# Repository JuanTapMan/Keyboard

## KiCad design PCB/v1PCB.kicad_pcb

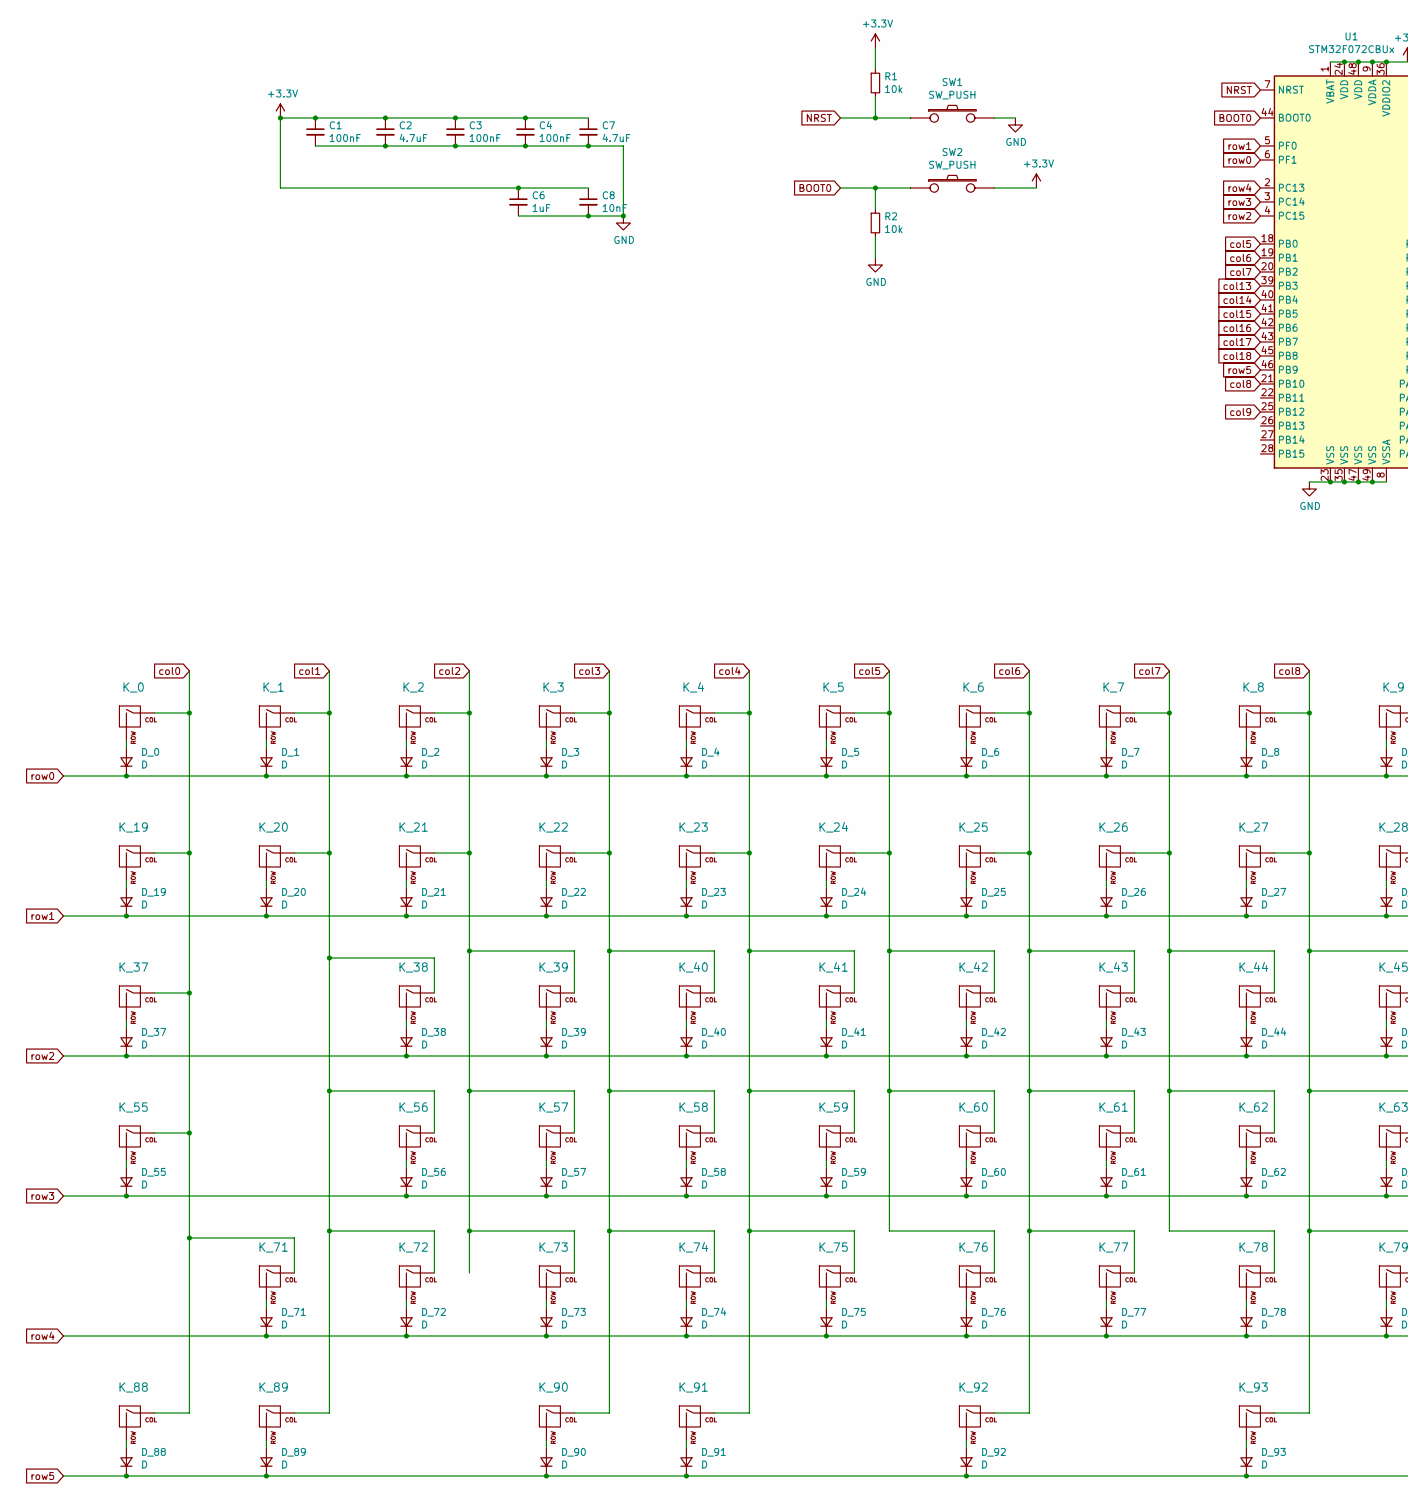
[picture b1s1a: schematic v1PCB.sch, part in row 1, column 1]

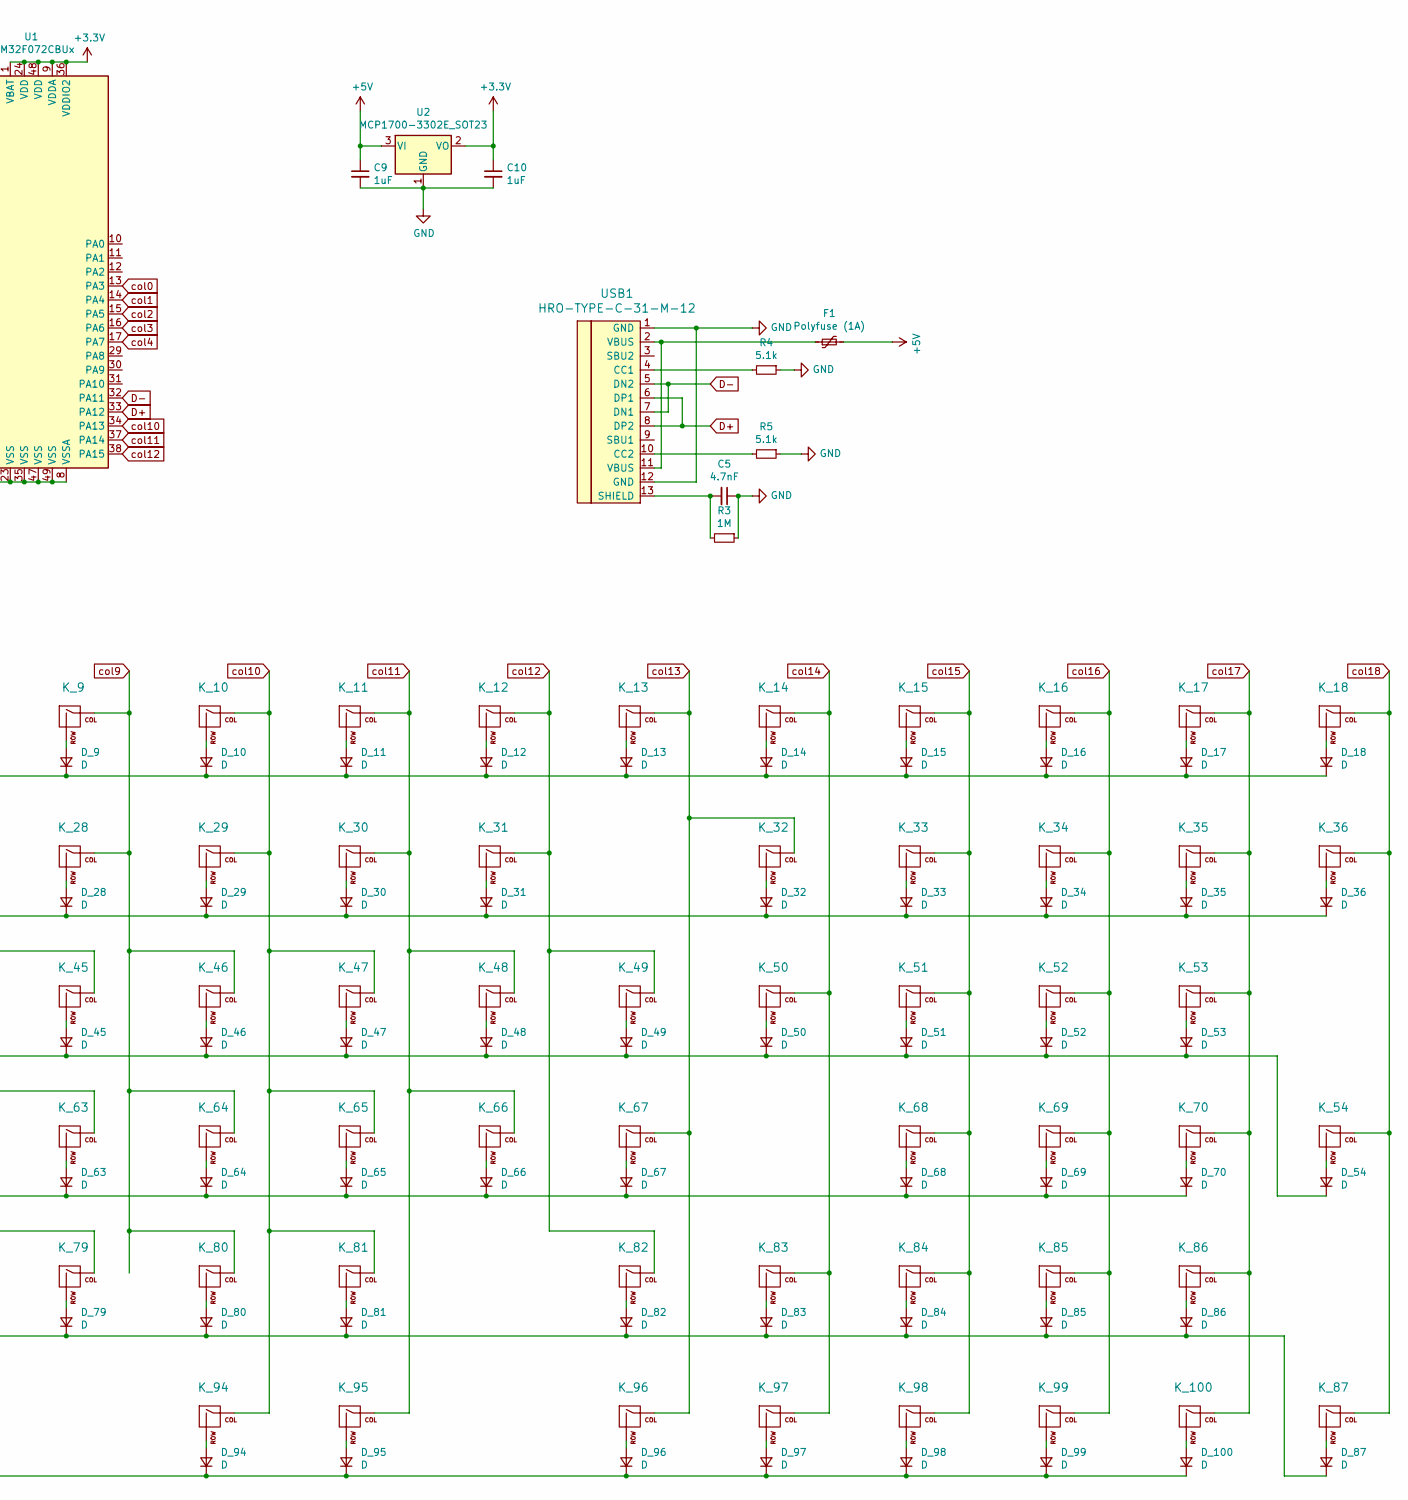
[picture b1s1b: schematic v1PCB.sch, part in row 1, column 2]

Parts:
C1, C3, C4: 100nF; C_0402_1005Metric
C2, C7: 4.7uF; C_0603_1608Metric
C5: 4.7nF; C_0603_1608Metric
C6: 1uF; C_0603_1608Metric
C8: 10nF; C_0402_1005Metric
C9, C10: 1uF; C_0402_1005Metric
D_0, D_1, D_2, D_3, D_4, D_5, D_6, D_7, D_8, D_9, D_10, D_11, D_12, D_13, D_14, D_15, D_16, D_17, D_18, D_19, D_20, D_21, D_22, D_23, D_24, D_25, D_26, D_27, D_28, D_29, D_30, D_31, D_32, D_33, D_34, D_35, D_36, D_37, D_38, D_39, D_40, D_41, D_42, D_43, D_44, D_45, D_46, D_47, D_48, D_49, D_50, D_51, D_52, D_53, D_54, D_55, D_56, D_57, D_58, D_59, D_60, D_61, D_62, D_63, D_64, D_65, D_66, D_67, D_68, D_69, D_70, D_71, D_72, D_73, D_74, D_75, D_76, D_77, D_78, D_79, D_80, D_81, D_82, D_83, D_84, D_85, D_86, D_87, D_88, D_89, D_90, D_91, D_92, D_93, D_94, D_95, D_96, D_97, D_98, D_99, D_100: D; D_SOD-123
F1: Polyfuse (1A); Fuse_0603_1608Metric
K_0, K_1, K_2, K_3, K_4, K_5, K_6, K_7, K_8, K_9, K_10, K_11, K_12, K_13, K_14, K_15, K_16, K_17, K_18, K_19, K_20, K_21, K_22, K_23, K_24, K_25, K_26, K_27, K_28, K_29, K_30, K_31, K_33, K_34, K_35, K_36, K_37, K_38, K_39, K_40, K_41, K_42, K_43, K_44, K_45, K_46, K_47, K_48, K_49, K_50, K_51, K_52, K_53, K_55, K_56, K_57, K_58, K_59, K_60, K_61, K_62, K_63, K_64, K_65, K_66, K_68, K_69, K_70, K_72, K_73, K_74, K_75, K_76, K_77, K_78, K_79, K_80, K_81, K_83, K_84, K_85, K_86, K_88, K_89, K_90, K_92, K_94, K_95, K_96, K_97, K_98, K_99, K_100: KEYSW; MXOnly-1U-NoLED
K_32, K_54, K_87: KEYSW; MXOnly-2U-NoLED
K_67, K_71, K_91: KEYSW; MXOnly-2.25U-NoLED
K_82: KEYSW; MXOnly-1.75U-NoLED
K_93: KEYSW; MXOnly-2.75U-NoLED
R1, R2: 10k; R_0805_2012Metric
R3: 1M; R_0805_2012Metric
R4, R5: 5.1k; R_0805_2012Metric
SW1, SW2: SW_PUSH; PushButton_6x6mm_TH
U1: STM32F072CBUx; QFN-48-1EP_7x7mm_P0.5mm_EP5.6x5.6mm
U2: MCP1700-3302E_SOT23; SOT-23
USB1: HRO-TYPE-C-31-M-12; HRO-TYPE-C-31-M-12-Assembly

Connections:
+3V3: C1.1, C2.1, C3.1, C4.1, C6.1, C7.1, C8.1, C10.1, R1.1, SW2.2, U1.1 (VBAT), U1.9 (VDDA), U1.24 (VDD), U1.36 (VDDIO2), U1.48 (VDD), U2.2 (VO)
+5V: C9.1, F1.2, U2.3 (VI)
BOOT0: R2.1, SW2.1, U1.44 (BOOT0)
D+: U1.33 (PA12), USB1.6 (DP1), USB1.8 (DP2)
D-: U1.32 (PA11), USB1.5 (DN2), USB1.7 (DN1)
GND: C1.2, C2.2, C3.2, C4.2, C5.1, C6.2, C7.2, C8.2, C9.2, C10.2, R2.2, R3.1, R4.1, R5.1, SW1.2, U1.8 (VSSA), U1.23 (VSS), U1.35 (VSS), U1.47 (VSS), U1.49 (VSS), U2.1 (GND), USB1.1 (GND), USB1.12 (GND)
NRST: R1.2, SW1.1, U1.7 (NRST)
unnamed: C5.2, R3.2, USB1.13 (SHIELD)
unnamed: D_0.2 (A), K_0.2 (ROW)
unnamed: D_1.2 (A), K_1.2 (ROW)
unnamed: D_2.2 (A), K_2.2 (ROW)
unnamed: D_3.2 (A), K_3.2 (ROW)
unnamed: D_4.2 (A), K_4.2 (ROW)
unnamed: D_5.2 (A), K_5.2 (ROW)
unnamed: D_6.2 (A), K_6.2 (ROW)
unnamed: D_7.2 (A), K_7.2 (ROW)
unnamed: D_8.2 (A), K_8.2 (ROW)
unnamed: D_9.2 (A), K_9.2 (ROW)
unnamed: D_10.2 (A), K_10.2 (ROW)
unnamed: D_11.2 (A), K_11.2 (ROW)
unnamed: D_12.2 (A), K_12.2 (ROW)
unnamed: D_13.2 (A), K_13.2 (ROW)
unnamed: D_14.2 (A), K_14.2 (ROW)
unnamed: D_15.2 (A), K_15.2 (ROW)
unnamed: D_16.2 (A), K_16.2 (ROW)
unnamed: D_17.2 (A), K_17.2 (ROW)
unnamed: D_18.2 (A), K_18.2 (ROW)
unnamed: D_19.2 (A), K_19.2 (ROW)
unnamed: D_20.2 (A), K_20.2 (ROW)
unnamed: D_21.2 (A), K_21.2 (ROW)
unnamed: D_22.2 (A), K_22.2 (ROW)
unnamed: D_23.2 (A), K_23.2 (ROW)
unnamed: D_24.2 (A), K_24.2 (ROW)
unnamed: D_25.2 (A), K_25.2 (ROW)
unnamed: D_26.2 (A), K_26.2 (ROW)
unnamed: D_27.2 (A), K_27.2 (ROW)
unnamed: D_28.2 (A), K_28.2 (ROW)
unnamed: D_29.2 (A), K_29.2 (ROW)
unnamed: D_30.2 (A), K_30.2 (ROW)
unnamed: D_31.2 (A), K_31.2 (ROW)
unnamed: D_32.2 (A), K_32.2 (ROW)
unnamed: D_33.2 (A), K_33.2 (ROW)
unnamed: D_34.2 (A), K_34.2 (ROW)
unnamed: D_35.2 (A), K_35.2 (ROW)
unnamed: D_36.2 (A), K_36.2 (ROW)
unnamed: D_37.2 (A), K_37.2 (ROW)
unnamed: D_38.2 (A), K_38.2 (ROW)
unnamed: D_39.2 (A), K_39.2 (ROW)
unnamed: D_40.2 (A), K_40.2 (ROW)
unnamed: D_41.2 (A), K_41.2 (ROW)
unnamed: D_42.2 (A), K_42.2 (ROW)
unnamed: D_43.2 (A), K_43.2 (ROW)
unnamed: D_44.2 (A), K_44.2 (ROW)
unnamed: D_45.2 (A), K_45.2 (ROW)
unnamed: D_46.2 (A), K_46.2 (ROW)
unnamed: D_47.2 (A), K_47.2 (ROW)
unnamed: D_48.2 (A), K_48.2 (ROW)
unnamed: D_49.2 (A), K_49.2 (ROW)
unnamed: D_50.2 (A), K_50.2 (ROW)
unnamed: D_51.2 (A), K_51.2 (ROW)
unnamed: D_52.2 (A), K_52.2 (ROW)
unnamed: D_53.2 (A), K_53.2 (ROW)
unnamed: D_54.2 (A), K_54.2 (ROW)
unnamed: D_55.2 (A), K_55.2 (ROW)
unnamed: D_56.2 (A), K_56.2 (ROW)
unnamed: D_57.2 (A), K_57.2 (ROW)
unnamed: D_58.2 (A), K_58.2 (ROW)
unnamed: D_59.2 (A), K_59.2 (ROW)
unnamed: D_60.2 (A), K_60.2 (ROW)
unnamed: D_61.2 (A), K_61.2 (ROW)
unnamed: D_62.2 (A), K_62.2 (ROW)
unnamed: D_63.2 (A), K_63.2 (ROW)
unnamed: D_64.2 (A), K_64.2 (ROW)
unnamed: D_65.2 (A), K_65.2 (ROW)
unnamed: D_66.2 (A), K_66.2 (ROW)
unnamed: D_67.2 (A), K_67.2 (ROW)
unnamed: D_68.2 (A), K_68.2 (ROW)
unnamed: D_69.2 (A), K_69.2 (ROW)
unnamed: D_70.2 (A), K_70.2 (ROW)
unnamed: D_71.2 (A), K_71.2 (ROW)
unnamed: D_72.2 (A), K_72.2 (ROW)
unnamed: D_73.2 (A), K_73.2 (ROW)
unnamed: D_74.2 (A), K_74.2 (ROW)
unnamed: D_75.2 (A), K_75.2 (ROW)
unnamed: D_76.2 (A), K_76.2 (ROW)
unnamed: D_77.2 (A), K_77.2 (ROW)
unnamed: D_78.2 (A), K_78.2 (ROW)
unnamed: D_79.2 (A), K_79.2 (ROW)
unnamed: D_80.2 (A), K_80.2 (ROW)
unnamed: D_81.2 (A), K_81.2 (ROW)
unnamed: D_82.2 (A), K_82.2 (ROW)
unnamed: D_83.2 (A), K_83.2 (ROW)
unnamed: D_84.2 (A), K_84.2 (ROW)
unnamed: D_85.2 (A), K_85.2 (ROW)
unnamed: D_86.2 (A), K_86.2 (ROW)
unnamed: D_87.2 (A), K_87.2 (ROW)
unnamed: D_88.2 (A), K_88.2 (ROW)
unnamed: D_89.2 (A), K_89.2 (ROW)
unnamed: D_90.2 (A), K_90.2 (ROW)
unnamed: D_91.2 (A), K_91.2 (ROW)
unnamed: D_92.2 (A), K_92.2 (ROW)
unnamed: D_93.2 (A), K_93.2 (ROW)
unnamed: D_94.2 (A), K_94.2 (ROW)
unnamed: D_95.2 (A), K_95.2 (ROW)
unnamed: D_96.2 (A), K_96.2 (ROW)
unnamed: D_97.2 (A), K_97.2 (ROW)
unnamed: D_98.2 (A), K_98.2 (ROW)
unnamed: D_99.2 (A), K_99.2 (ROW)
unnamed: D_100.2 (A), K_100.2 (ROW)
unnamed: F1.1, USB1.2 (VBUS), USB1.11 (VBUS)
unnamed: R4.2, USB1.4 (CC1)
unnamed: R5.2, USB1.10 (CC2)
col0: K_0.1 (COL), K_19.1 (COL), K_37.1 (COL), K_55.1 (COL), K_71.1 (COL), K_88.1 (COL), U1.13 (PA3)
col1: K_1.1 (COL), K_20.1 (COL), K_38.1 (COL), K_56.1 (COL), K_72.1 (COL), K_89.1 (COL), U1.14 (PA4)
col2: K_2.1 (COL), K_21.1 (COL), K_39.1 (COL), K_57.1 (COL), K_73.1 (COL), U1.15 (PA5)
col3: K_3.1 (COL), K_22.1 (COL), K_40.1 (COL), K_58.1 (COL), K_74.1 (COL), K_90.1 (COL), U1.16 (PA6)
col4: K_4.1 (COL), K_23.1 (COL), K_41.1 (COL), K_59.1 (COL), K_75.1 (COL), K_91.1 (COL), U1.17 (PA7)
col5: K_5.1 (COL), K_24.1 (COL), K_42.1 (COL), K_60.1 (COL), K_76.1 (COL), U1.18 (PB0)
col6: K_6.1 (COL), K_25.1 (COL), K_43.1 (COL), K_61.1 (COL), K_77.1 (COL), K_92.1 (COL), U1.19 (PB1)
col7: K_7.1 (COL), K_26.1 (COL), K_44.1 (COL), K_62.1 (COL), K_78.1 (COL), U1.20 (PB2)
col8: K_8.1 (COL), K_27.1 (COL), K_45.1 (COL), K_63.1 (COL), K_79.1 (COL), K_93.1 (COL), U1.21 (PB10)
col9: K_9.1 (COL), K_28.1 (COL), K_46.1 (COL), K_64.1 (COL), K_80.1 (COL), U1.25 (PB12)
col10: K_10.1 (COL), K_29.1 (COL), K_47.1 (COL), K_65.1 (COL), K_81.1 (COL), K_94.1 (COL), U1.34 (PA13)
col11: K_11.1 (COL), K_30.1 (COL), K_48.1 (COL), K_66.1 (COL), K_95.1 (COL), U1.37 (PA14)
col12: K_12.1 (COL), K_31.1 (COL), K_49.1 (COL), K_82.1 (COL), U1.38 (PA15)
col13: K_13.1 (COL), K_32.1 (COL), K_67.1 (COL), K_96.1 (COL), U1.39 (PB3)
col14: K_14.1 (COL), K_50.1 (COL), K_83.1 (COL), K_97.1 (COL), U1.40 (PB4)
col15: K_15.1 (COL), K_33.1 (COL), K_51.1 (COL), K_68.1 (COL), K_84.1 (COL), K_98.1 (COL), U1.41 (PB5)
col16: K_16.1 (COL), K_34.1 (COL), K_52.1 (COL), K_69.1 (COL), K_85.1 (COL), K_99.1 (COL), U1.42 (PB6)
col17: K_17.1 (COL), K_35.1 (COL), K_53.1 (COL), K_70.1 (COL), K_86.1 (COL), K_100.1 (COL), U1.43 (PB7)
col18: K_18.1 (COL), K_36.1 (COL), K_54.1 (COL), K_87.1 (COL), U1.45 (PB8)
row0: D_0.1 (K), D_1.1 (K), D_2.1 (K), D_3.1 (K), D_4.1 (K), D_5.1 (K), D_6.1 (K), D_7.1 (K), D_8.1 (K), D_9.1 (K), D_10.1 (K), D_11.1 (K), D_12.1 (K), D_13.1 (K), D_14.1 (K), D_15.1 (K), D_16.1 (K), D_17.1 (K), D_18.1 (K), U1.6 (PF1)
row1: D_19.1 (K), D_20.1 (K), D_21.1 (K), D_22.1 (K), D_23.1 (K), D_24.1 (K), D_25.1 (K), D_26.1 (K), D_27.1 (K), D_28.1 (K), D_29.1 (K), D_30.1 (K), D_31.1 (K), D_32.1 (K), D_33.1 (K), D_34.1 (K), D_35.1 (K), D_36.1 (K), U1.5 (PF0)
row2: D_37.1 (K), D_38.1 (K), D_39.1 (K), D_40.1 (K), D_41.1 (K), D_42.1 (K), D_43.1 (K), D_44.1 (K), D_45.1 (K), D_46.1 (K), D_47.1 (K), D_48.1 (K), D_49.1 (K), D_50.1 (K), D_51.1 (K), D_52.1 (K), D_53.1 (K), D_54.1 (K), U1.4 (PC15)
row3: D_55.1 (K), D_56.1 (K), D_57.1 (K), D_58.1 (K), D_59.1 (K), D_60.1 (K), D_61.1 (K), D_62.1 (K), D_63.1 (K), D_64.1 (K), D_65.1 (K), D_66.1 (K), D_67.1 (K), D_68.1 (K), D_69.1 (K), D_70.1 (K), U1.3 (PC14)
row4: D_71.1 (K), D_72.1 (K), D_73.1 (K), D_74.1 (K), D_75.1 (K), D_76.1 (K), D_77.1 (K), D_78.1 (K), D_79.1 (K), D_80.1 (K), D_81.1 (K), D_82.1 (K), D_83.1 (K), D_84.1 (K), D_85.1 (K), D_86.1 (K), D_87.1 (K), U1.2 (PC13)
row5: D_88.1 (K), D_89.1 (K), D_90.1 (K), D_91.1 (K), D_92.1 (K), D_93.1 (K), D_94.1 (K), D_95.1 (K), D_96.1 (K), D_97.1 (K), D_98.1 (K), D_99.1 (K), D_100.1 (K), U1.46 (PB9)

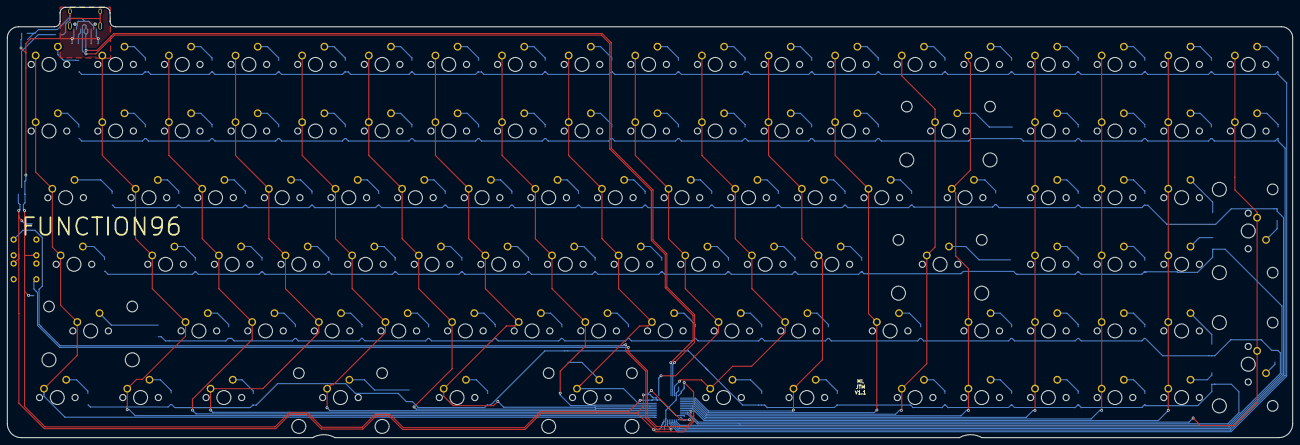
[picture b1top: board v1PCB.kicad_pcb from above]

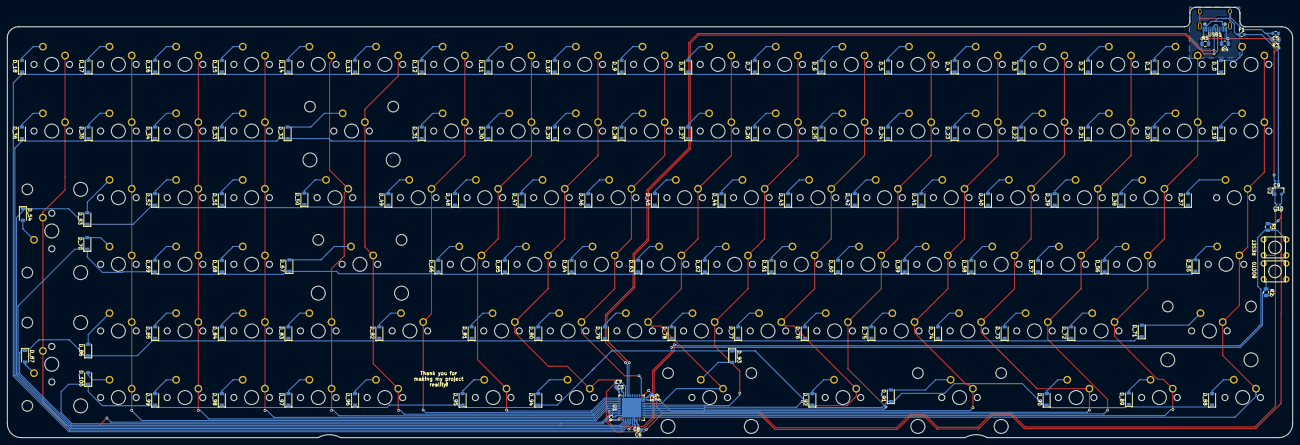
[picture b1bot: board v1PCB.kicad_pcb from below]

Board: 2 copper layers, 367.5 x 123.0 mm, 223 parts (122 on the bottom side), 137 nets.

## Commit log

2020-07-20 Schematic and PCB partially done, add Micro USB
2020-07-20 Changed from 5V to GND. Still need to add USB
2020-07-20 Removed ratsnest, need to fix all runs to vddio, need USB
2020-07-20 Fixed a few runs, still need to add USB and redo VDDIO decoupling capacitors
2020-07-21 Almost done with cap placement, still neeed to add USBC
2020-07-21 Finished schematic, begin drawing traces
2020-07-21 Need to finish reset buttons, confirm routing of 3V3 and GND, review overall package
2020-07-21 Added switches, fixed most DRC issues. Only questions about GNDleft
2020-07-22 Review and clean
2020-07-22 Added rounded corners, fixed most USB line issues
2020-07-22 Added ground fills around USBC
2020-07-22 Still need review, otherwise minor edits for the most part
2020-07-22 Moved MCU so that stabs won't interfere. Almost cried.
2020-07-22 Minor edits to cap values. Read previous comments
2020-07-22 Starting Plate
2020-07-22 Adding components for visual aid
2020-07-22 Reorganizing
2020-07-22 Added PCB cutouts, added CAD files for the case.
2020-07-22 Redo all traces because MCU got moved to bottom. Continue refining CAD model.
2020-07-23 Finished relocating MCU, prep for review. Need to adjust cutouts for case mounting.
2020-07-23 added GND fill
2020-07-23 Rerouted some traces near stab holes
2020-07-23 Fixed cutouts.
2020-07-23 minor edits
2020-07-23 Continued working on CAD, PCB still needs to be reviewed.
2020-07-23 Redid USB data line routing at the USB port
2020-07-23 Most of the CAD work is done, add screws to the bottom/top and add switches. Find caps?
2020-07-23 See previous notes. Added a few renders
2020-07-23 Rough CAD and schematics done. Continue refining.
2020-07-23 Double-checking
2020-07-24 PCB is being produced, because fuck it. CAD is being quoted.
2020-07-24 Double checking
2020-07-24 Added CAD drawings for machining
2020-07-24 Fixed alignment between top and bottom plates. Need to send updated drawings and CAD to machinist
2020-07-24 Polished up
2020-07-25 Continued refinement. Fixed top plate alignments.
2020-07-25 Updated some components
2020-07-27 Added renders and fixed Plate for stabs.
2020-08-02 Updates to CAD and PCB
2020-08-02 More updates
2020-08-06 Nearing final production
2020-08-07 Final CAD models and PCB's are almost ready
2020-08-07 Updated drawings
2020-08-16 Updates to CAD/Drawings
2020-08-18 Updates to PCB and CAD. Incorrect PaP files, beware EasyEDA
2020-08-30 Updates to CAD
2020-09-23 Logo Added to Export
2020-10-21 Various Updates
